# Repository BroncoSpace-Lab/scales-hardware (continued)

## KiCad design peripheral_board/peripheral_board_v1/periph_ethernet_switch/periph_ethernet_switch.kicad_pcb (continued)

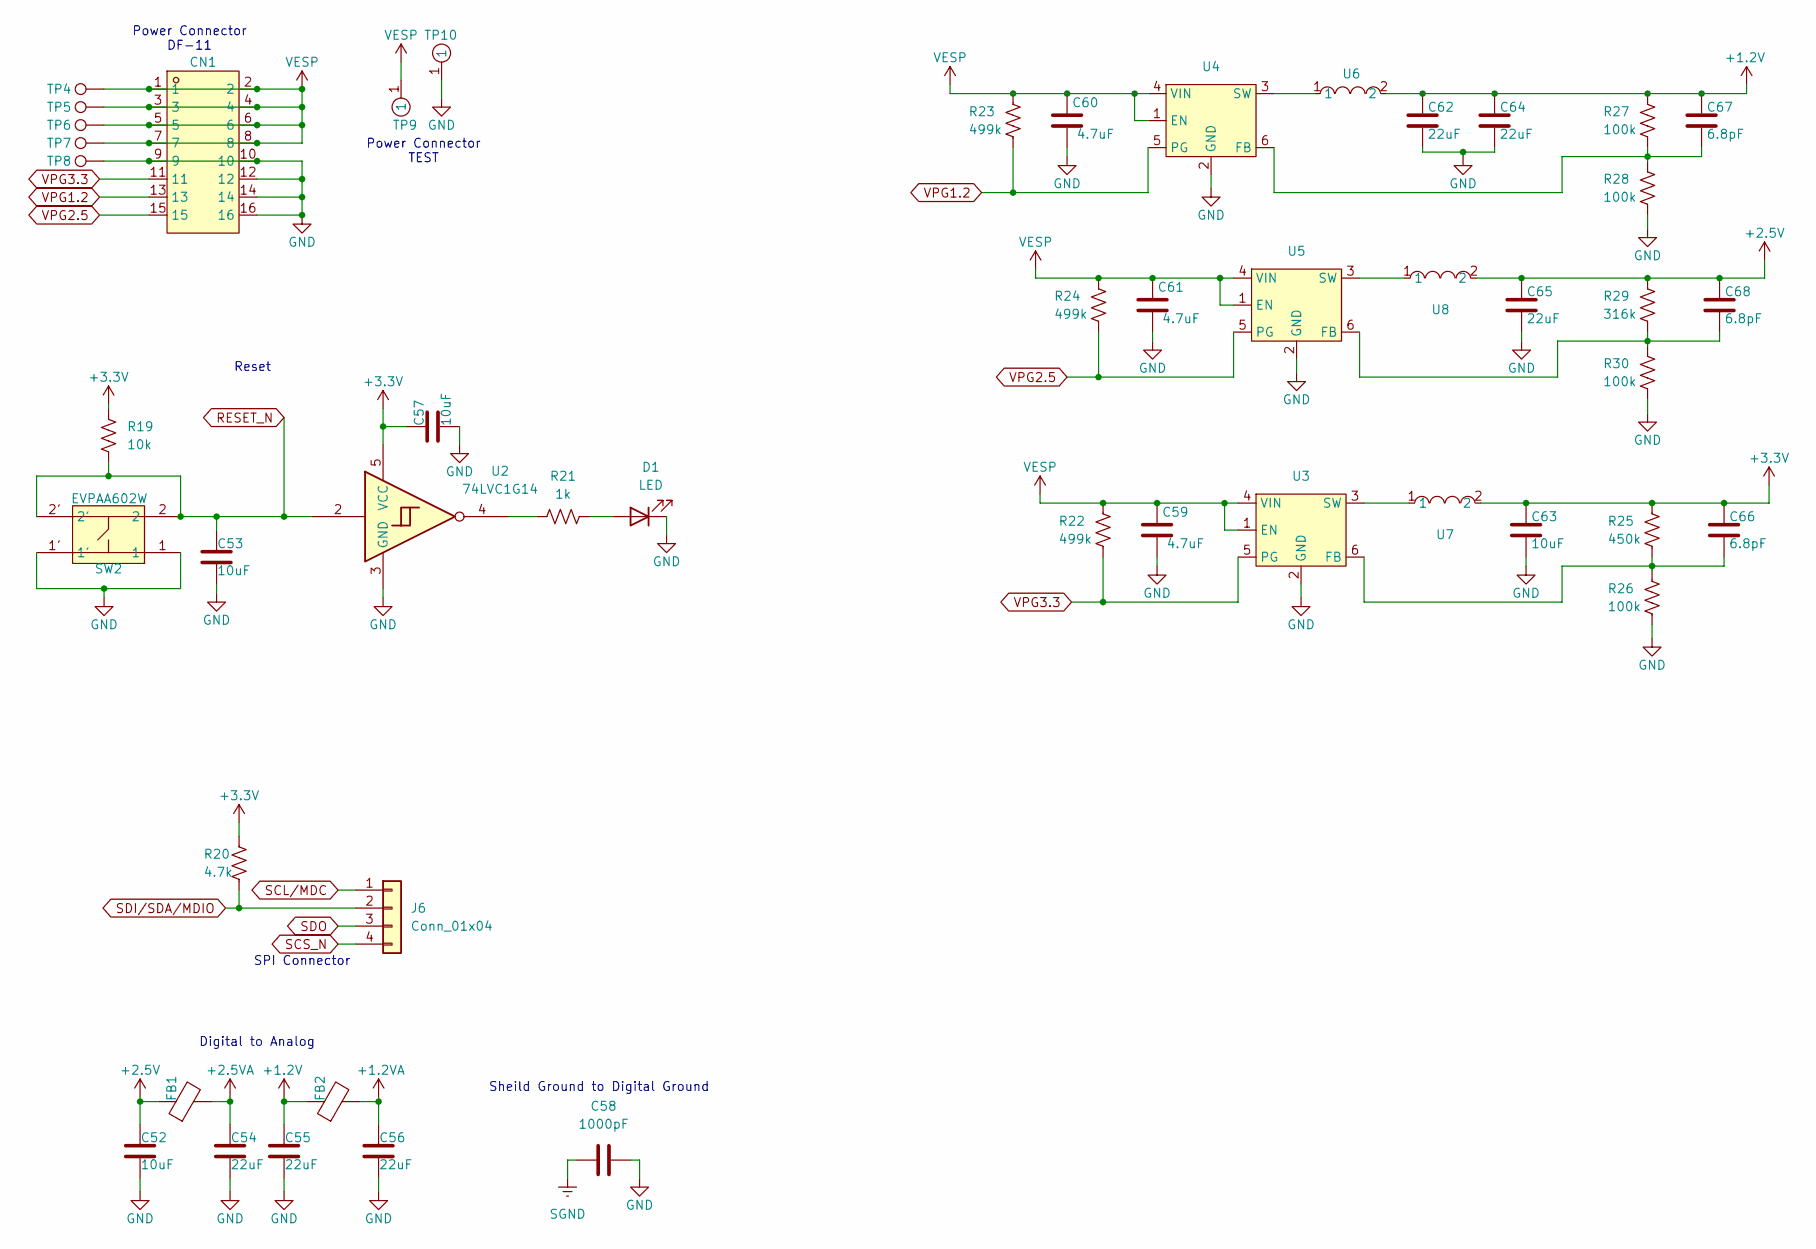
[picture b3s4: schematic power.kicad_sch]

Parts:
C52, C53, C57, C63: 10uF; C_0603_1608Metric
C54, C55, C56, C62, C64, C65: 22uF; C_0603_1608Metric
C58: 1000pF; C_1210_3225Metric
C59, C60, C61: 4.7uF; C_0603_1608Metric
C66, C67, C68: 6.8pF; C_0603_1608Metric
CN1: DF11-16DP-2DSA(08); CONN-TH_DF11-16DP-2DSA-08; LCSC Part C530981
D1: LED; LED0603-RD
FB1, FB2: FerriteBead; L_0805_2012Metric
J6: Conn_01x04; PinHeader_1x04_P2.54mm_Vertical
R19: 10k; R_0603_1608Metric
R20: 4.7k; R_0603_1608Metric
R21: 1k; R_0603_1608Metric
R22, R23, R24: 499k; R_0603_1608Metric
R25: 450k; R_0603_1608Metric
R26, R27, R28, R30: 100k; R_0603_1608Metric
R29: 316k; R_0603_1608Metric
SW2: EVPAA602W; KEY-TH_4P-L3.5-W4.9-P2.80-LS4.3; LCSC Part C79148
TP4, TP5, TP6, TP7, TP8: TestPoint; TestPoint_Pad_1.0x1.0mm
TP9, TP10: RH-5001; TEST-TH_BD2.54-P1.4_BLACK; LCSC Part C5199801
U2: 74LVC1G14; SOT-23-5
U3, U4, U5: TLV62569PDDCR; SOT-23-6_L2.9-W1.6-P0.95-LS2.8-BL; LCSC Part C398365
U6, U7, U8: XAL4020-222MEC; IND-SMD_L4.0-W4.0-A; LCSC Part C3151182

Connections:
+1.2V: C55.1, C62.1, C64.1, C67.1, FB2.1, R27.2, U6.2; also elsewhere on the board
+1.2VA: C56.1, FB2.2; also elsewhere on the board
+2.5V: C52.1, C65.1, C68.1, FB1.1, R29.2, U8.2
+2.5VA: C54.1, FB1.2; also elsewhere on the board
unnamed: D1.2 (A), R21.1
unnamed: R21.2, U2.4
unnamed: U3.3 (SW), U7.1
unnamed: C67.2, R27.1, R28.2, U4.6 (FB)
unnamed: U4.3 (SW), U6.1
unnamed: C68.2, R29.1, R30.2, U5.6 (FB)
unnamed: U5.3 (SW), U8.1
RESET_N: C53.1, R19.1, SW2.2, SW2.2', U2.2; also elsewhere on the board
SCL/MDC: J6.1; also elsewhere on the board
SCS_N: J6.4; also elsewhere on the board
SDI/SDA/MDIO: J6.2, R20.1; also elsewhere on the board
SDO: J6.3; also elsewhere on the board
SGND: C58.1; also elsewhere on the board
VESP: C59.1, C60.1, C61.1, CN1.1, CN1.2, CN1.3, CN1.4, CN1.5, CN1.6, CN1.7, CN1.8, R22.2, R23.2, R24.2, TP4.1, TP5.1, TP6.1, TP7.1, TP9.1, U3.1 (EN), U3.4 (VIN), U4.1 (EN), U4.4 (VIN), U5.1 (EN), U5.4 (VIN)
VPG1.2: CN1.13, R23.1, U4.5 (PG)
VPG2.5: CN1.15, R24.1, U5.5 (PG)
VPG3.3: CN1.11, R22.1, U3.5 (PG)

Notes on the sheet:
Reset
SPI Connector
Sheild Ground to Digital Ground
Digital to Analog
Power Connector DF-11
Power Connector TEST

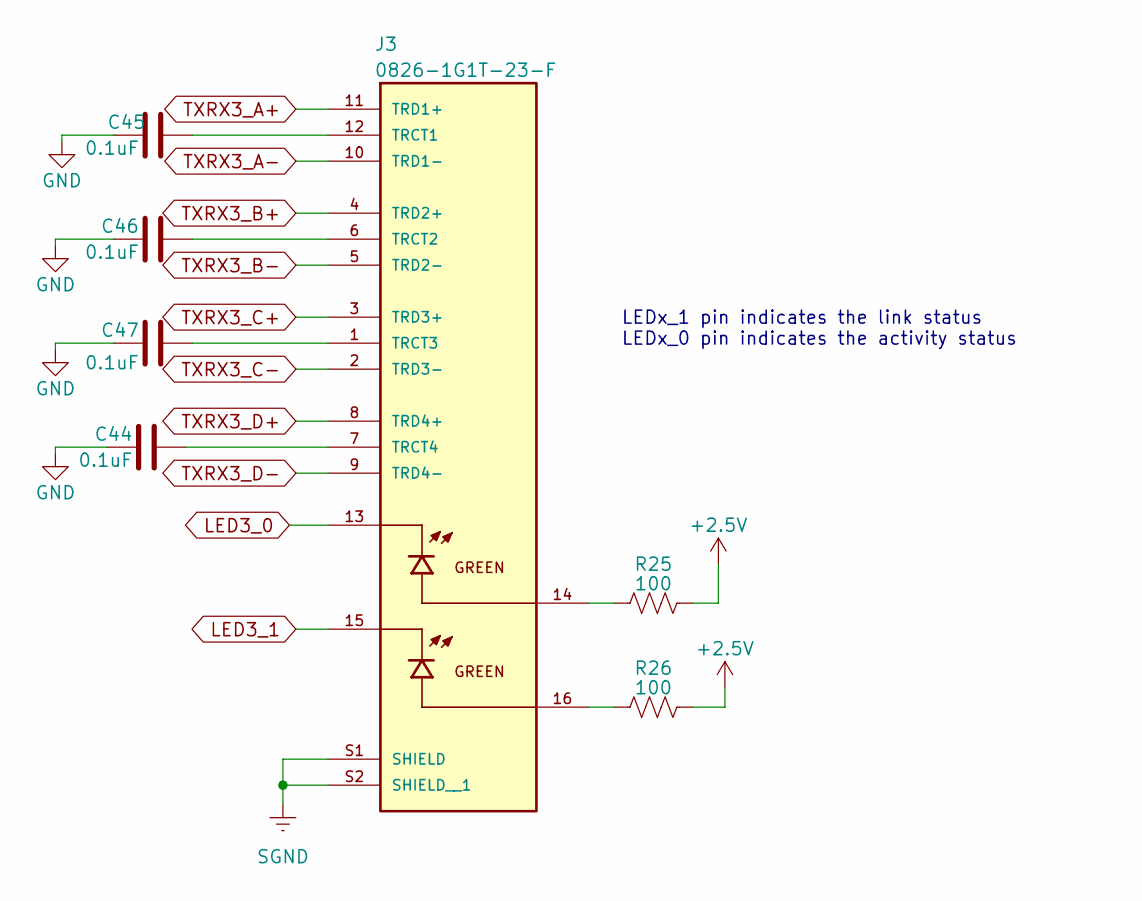
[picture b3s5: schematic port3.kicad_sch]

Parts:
C44, C45, C46, C47: 0.1uF; C_0603_1608Metric
J3: 0826-1G1T-23-F; BEL_0826-1G1T-23-F
R25, R26: 100; R_0603_1608Metric

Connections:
LED3_0: J3.13; also elsewhere on the board
LED3_1: J3.15; also elsewhere on the board
SGND: J3.S1 (SHIELD), J3.S2 (SHIELD__1); also elsewhere on the board
TXRX3_A+: J3.11 (TRD1+); also elsewhere on the board
TXRX3_A-: J3.10 (TRD1-); also elsewhere on the board
TXRX3_B+: J3.4 (TRD2+); also elsewhere on the board
TXRX3_B-: J3.5 (TRD2-); also elsewhere on the board
TXRX3_C+: J3.3 (TRD3+); also elsewhere on the board
TXRX3_C-: J3.2 (TRD3-); also elsewhere on the board
TXRX3_D+: J3.8 (TRD4+); also elsewhere on the board
TXRX3_D-: J3.9 (TRD4-); also elsewhere on the board

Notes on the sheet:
LEDx_1 pin indicates the link status LEDx_0 pin indicates the activity status

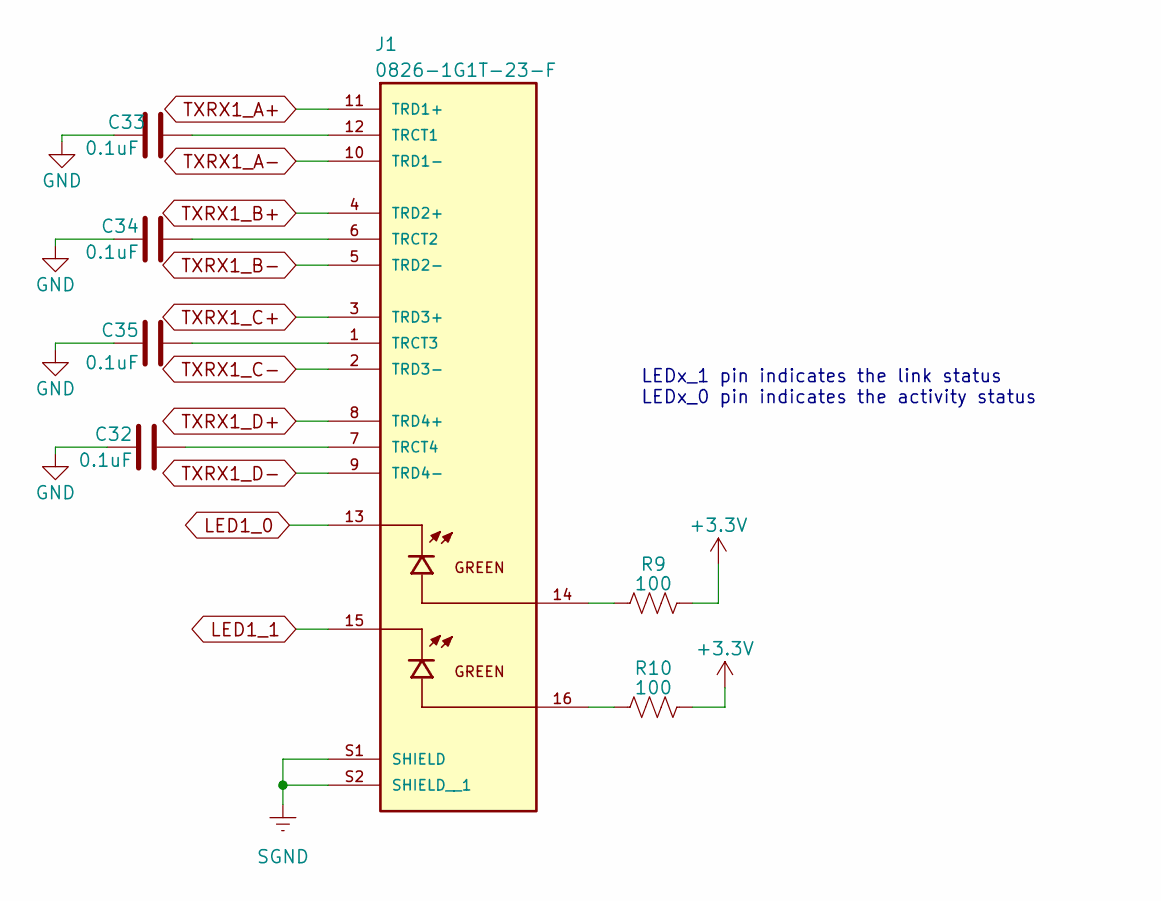
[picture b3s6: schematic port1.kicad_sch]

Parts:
C32, C33, C34, C35: 0.1uF; C_0603_1608Metric
J1: 0826-1G1T-23-F; BEL_0826-1G1T-23-F
R9, R10: 100; R_0603_1608Metric

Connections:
LED1_0: J1.13; also elsewhere on the board
LED1_1: J1.15; also elsewhere on the board
unnamed: J1.14, R9.2
unnamed: J1.16, R10.2
unnamed: C33.2, J1.12 (TRCT1)
unnamed: C34.2, J1.6 (TRCT2)
unnamed: C35.2, J1.1 (TRCT3)
unnamed: C32.2, J1.7 (TRCT4)
SGND: J1.S1 (SHIELD), J1.S2 (SHIELD__1); also elsewhere on the board
TXRX1_A+: J1.11 (TRD1+); also elsewhere on the board
TXRX1_A-: J1.10 (TRD1-); also elsewhere on the board
TXRX1_B+: J1.4 (TRD2+); also elsewhere on the board
TXRX1_B-: J1.5 (TRD2-); also elsewhere on the board
TXRX1_C+: J1.3 (TRD3+); also elsewhere on the board
TXRX1_C-: J1.2 (TRD3-); also elsewhere on the board
TXRX1_D+: J1.8 (TRD4+); also elsewhere on the board
TXRX1_D-: J1.9 (TRD4-); also elsewhere on the board

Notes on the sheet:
LEDx_1 pin indicates the link status LEDx_0 pin indicates the activity status

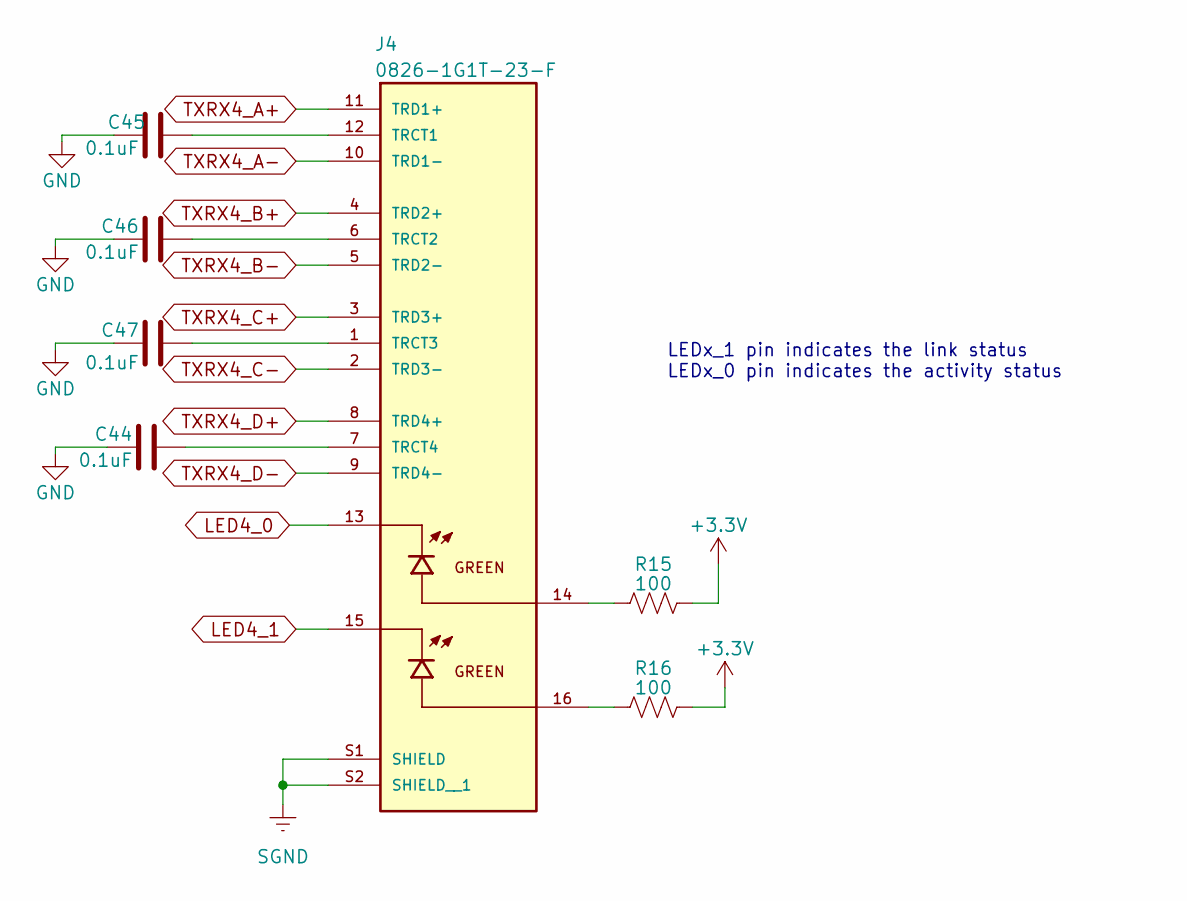
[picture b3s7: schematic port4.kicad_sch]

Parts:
C44, C45, C46, C47: 0.1uF; C_0603_1608Metric
J4: 0826-1G1T-23-F; BEL_0826-1G1T-23-F
R15, R16: 100; R_0603_1608Metric

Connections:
LED4_0: J4.13; also elsewhere on the board
LED4_1: J4.15; also elsewhere on the board
unnamed: J4.14, R15.2
unnamed: J4.16, R16.2
SGND: J4.S1 (SHIELD), J4.S2 (SHIELD__1); also elsewhere on the board
TXRX4_A+: J4.11 (TRD1+); also elsewhere on the board
TXRX4_A-: J4.10 (TRD1-); also elsewhere on the board
TXRX4_B+: J4.4 (TRD2+); also elsewhere on the board
TXRX4_B-: J4.5 (TRD2-); also elsewhere on the board
TXRX4_C+: J4.3 (TRD3+); also elsewhere on the board
TXRX4_C-: J4.2 (TRD3-); also elsewhere on the board
TXRX4_D+: J4.8 (TRD4+); also elsewhere on the board
TXRX4_D-: J4.9 (TRD4-); also elsewhere on the board

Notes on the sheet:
LEDx_1 pin indicates the link status LEDx_0 pin indicates the activity status

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
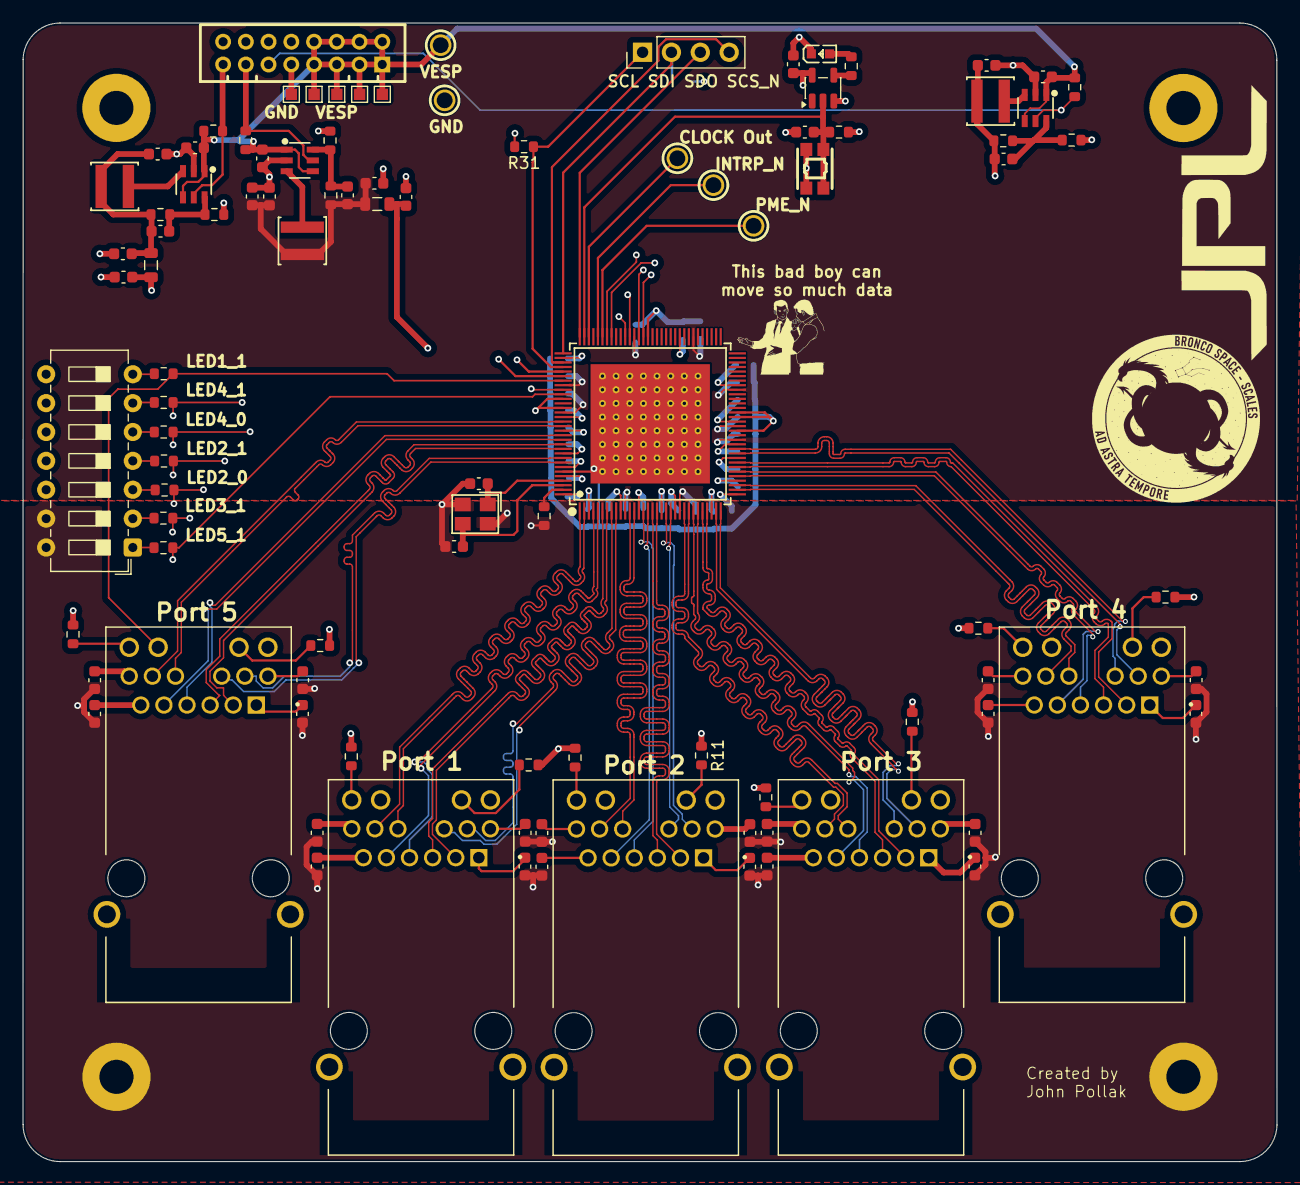
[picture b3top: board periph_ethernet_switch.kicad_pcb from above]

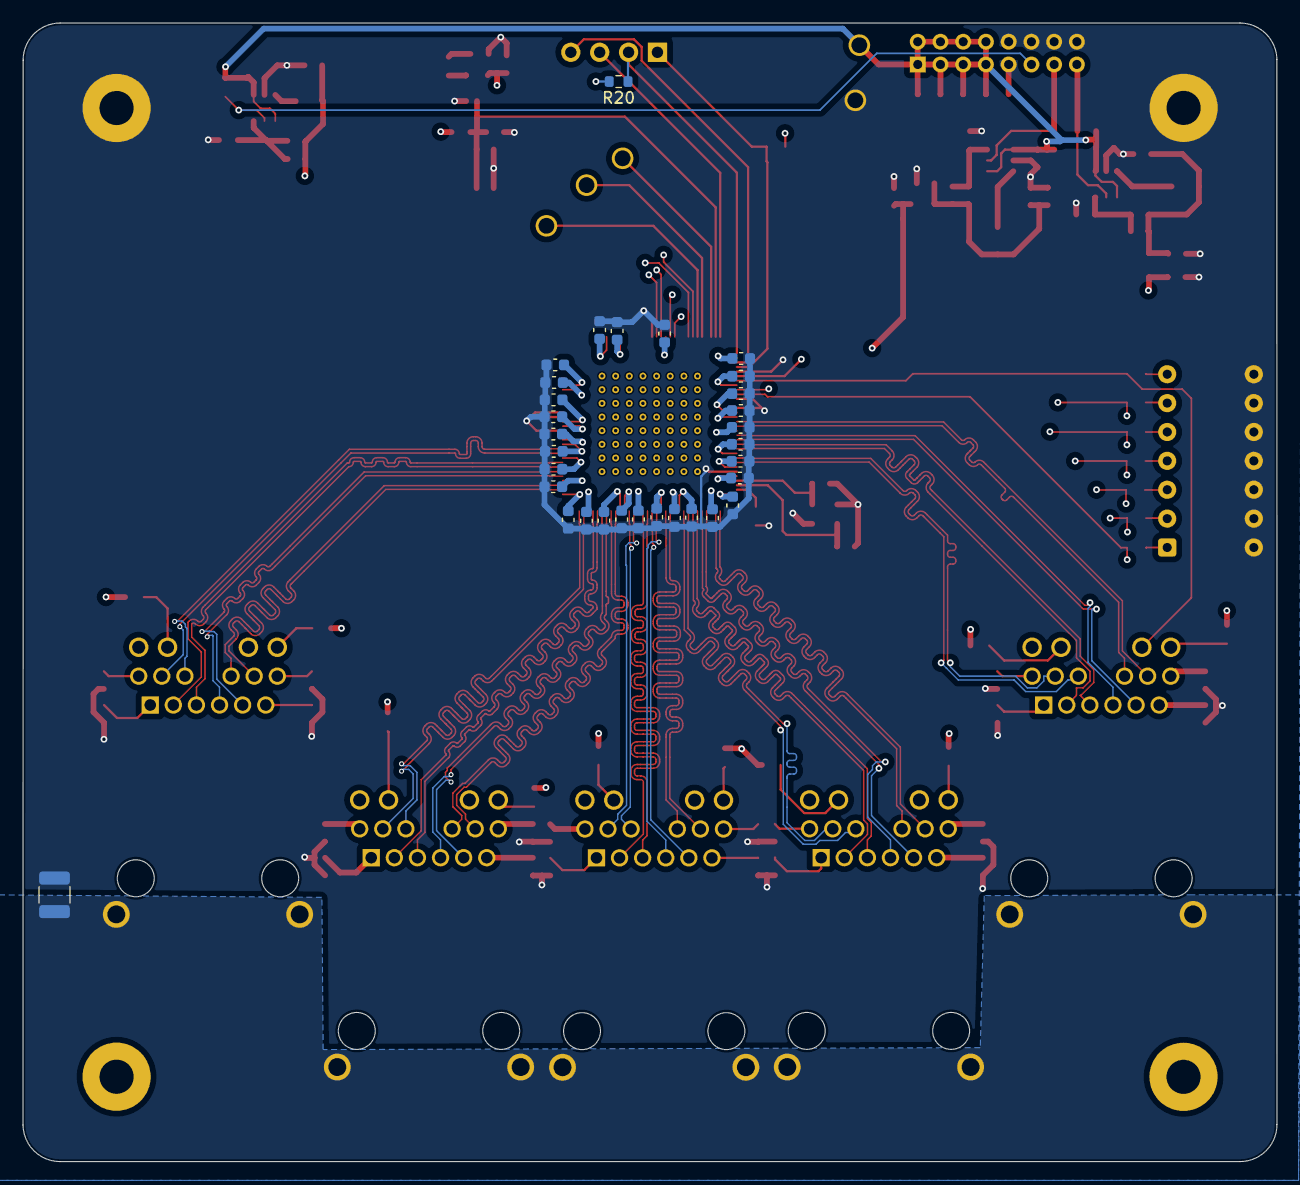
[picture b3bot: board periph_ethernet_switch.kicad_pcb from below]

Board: 6 copper layers, 110.3 x 100.2 mm, 134 parts (31 on the bottom side), 117 nets.

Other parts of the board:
C40, C41, C42, C43: 0.1uF; C_0603_1608Metric
R13, R14: 100; R_0603_1608Metric
R31: 4.7k; R_0603_1608Metric

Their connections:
SCL/MDC: R31.1; also elsewhere on the board

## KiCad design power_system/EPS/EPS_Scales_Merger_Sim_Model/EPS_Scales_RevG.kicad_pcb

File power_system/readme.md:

- **Viking 1-C Board Ordered (7/9/25)**
    
    This is the third board of the SCALES EPS. It is based on the RevF schematic which yields the Viking 1-C Board. This board improves on the success of the 1-B board and implements some minor improvements that prevented the Peripheral and Jetson subsystem from activating correctly. 
    
    **List of Changes in Viking 1-C After Production Errors in Viking 1-B**
    
    - Removed R48
    - Removed R83
    - The above mentioned resistors caused too low of a voltage to fully enable the En pins on the load switches, and by simply removing them we can successfully drive the load switches on using GPIO pins.
    - Added 3 MCP9808 I2C Temperature Sensors so we can have some on board temp monitoring, I made sure the addresses dont conflict with that of the other i2c devices on board.
    
    **EPS REV F/ Viking 1-C System Overview:**
    
    - Power Requirements (+28v 8A Max)
        - ML/Edge Computer - Nvidia Jetson (+20V 4A)
        - OBC/Flight Computer - IMX8 (+3.3V 2A)
        - Peripheral System - Raspberry Pi + Wiznet (+5V 2A)
    - Component List
        - Load Switch + Controller: [TPS1HA08-Q1](https://www.ti.com/lit/ds/symlink/tps1ha08-q1.pdf?ts=1748448912035&ref_url=https%253A%252F%252Fwww.ti.com%252Fproduct%252FTPS1HA08-Q1)
        - Switching Regulator: [LT8612](https://jlcpcb.com/api/file/downloadByFileSystemAccessId/8589836477510287360)
        - IV-Sensor: [INA260AIPWR](https://jlcpcb.com/api/file/downloadByFileSystemAccessId/8589836477510287360)
        - Temperature Sensor: [MCP9808](https://www.microchip.com/en-us/product/mcp9800)
        - Clock Generator: [LTC6902](https://www.analog.com/media/en/technical-documentation/data-sheets/6902f.pdf)
        - I2C Buffer: [TCA4307](https://www.ti.com/lit/ds/symlink/tca4307.pdf?HQS=dis-dk-null-digikeymode-dsf-pf-null-wwe&ts=1748986173530&ref_url=https%253A%252F%252Fwww.ti.com%252Fgeneral%252Fdocs%252Fsuppproductinfo.tsp%253FdistId%253D10%2526gotoUrl%253Dhttps%253A%252F%252Fwww.ti.com%252Flit%252Fgpn%252Ftca4307)
        - Comparator (WD Circuit): [TLV1704](https://www.ti.com/lit/ds/symlink/tlv1704-sep.pdf)
        - Subsystem Connector: [DF-11 (2x8)](https://www.lcsc.com/product-detail/Wire-To-Board-Wire-To-Wire-Connector_HRS-Hirose-HRS-DF11-16DP-2DSA-08_C530981.html)
        - Power Connector: [XT-60PWF](https://www.lcsc.com/product-detail/plug_Changzhou-Amass-Elec-XT60PW-F_C428722.html)
    - Concept of Operations
        - OBC is the primary subsystem, which is always enabled. The OBC controls the ML and Perif. via load switches. OBC must hold the respective subsystem EN pin high for it to be active.
        - Each subsystem has a Watch dog that verifies its normal operation; in the case of a fault, the subsystem is disabled by its watch dog.
            - OBC: If the OBC hangs and fails to pet, it is power cycled, as the EN pin for its load switch is always held high with respect to the battery voltage
            - ML/Perif: If either of these subsystems hang and fail to pet, they are disabled until the OBC re-enables them.
        - Monitoring is done by the OBC via I2C from the INA260s, which allows the subsystem to get basic telemetry on the subsystem state of operation
        - There are also 3 seperate temperature sensors that send telemetry back to the IMX8X over a 3.3v I2C
    
    **Block Diagram and Visual Con. Ops**
    
    - EPS RevF Block Diagram

    - EPS RevF Concept of Operations

    **Board Schematic**
    
    - Root

    - OBC Subsystem

    - Perif. Subsystem

    - Jetson Subsystem

    - OBC Watchdog Circuit

    - Peripheral Watchdog Circuit

    - Jetson Watchdog Circuit

    **Board Layout**
    
    - Signal1 Layer

    - GND Layer

    - Power Layer

    - Signal2 Layer

    **3D Render Front and Back**
    
    - Front

    - Back

###  Viking 1-B Board Ordered (6/20/25) ###
This is the second board of the SCALES EPS. It is based on the RevE schematic which yields the Viking 1-B Board. It seeks to improve on numerous calculation and placement errors in the first prototype. Particularly miscalculated resistor and inductor values as well as significant improvements in placement, routing, fills, and smaller components.

### List of Changes in Viking 1-B After Production Errors in Viking 1-A ###
* R66 was incorrect in 1-A, should have been a 100k, was a 10k instead. Fixed in this revision
* L2 was 8.2uH, should have been 6.1uH (OBC Subsystem)
* L1 was 12uH, should have been 10uH (Perif. Subsystem)
* L3 was 4.7uH, should have been 47uH (Jetson Subsystem)
* Most capacitors were changed to 50V/35V rated 0603 caps, any others are 10v 0402 caps.
* Small change to the Jetson WD circuit, adding a voltage divider to make the voltage safe for the the 10v 0402 caps
* Soft start capacitor was changed for each subsystem, set to 2.2uF for about 1 second. Using the V(t) = (I/C) * t equation, rearrange for t, and I is 2.1*10^-6, C is 2.2uF, and V(t) is 0.97v.
* LEDs on ST pin for all load switches were rearranged for (hopefully) proper fault indication
* 4.7k resistor removed for the I2C buffer
* Connectors were changed for identical variants of the 2*8 Df11 due to low stock
* D1N141WS diodes were changes to D1N4448WS diodes. Almost identical, same package
* Replaced mounting holes with slightly larger ones to match the M2.5 Spec (2.7mm hole diameter)

## EPS_REVE / Viking 1-BSystem Overview: ##

- Power Requirements (+28v 8A Max)
    - ML/Edge Computer - Nvidia Jetson (+20V 4A)
    - OBC/Flight Computer - IMX8 (+3.3V 2A)
    - Peripheral System - Raspberry Pi + Wiznet (+5V 2A)
- Component List
    - Load Switch + Controller: [TPS1HA08-Q1](https://www.ti.com/lit/ds/symlink/tps1ha08-q1.pdf?ts=1748448912035&ref_url=https%253A%252F%252Fwww.ti.com%252Fproduct%252FTPS1HA08-Q1)
    - Switching Regulator: [LT8612](https://jlcpcb.com/api/file/downloadByFileSystemAccessId/8589836477510287360)
    - IV-Sensor: [INA260AIPWR](https://jlcpcb.com/api/file/downloadByFileSystemAccessId/8589836477510287360)
    - Clock Generator: [LTC6902](https://www.analog.com/media/en/technical-documentation/data-sheets/6902f.pdf)
    - I2C Buffer: [TCA4307](https://www.ti.com/lit/ds/symlink/tca4307.pdf?HQS=dis-dk-null-digikeymode-dsf-pf-null-wwe&ts=1748986173530&ref_url=https%253A%252F%252Fwww.ti.com%252Fgeneral%252Fdocs%252Fsuppproductinfo.tsp%253FdistId%253D10%2526gotoUrl%253Dhttps%253A%252F%252Fwww.ti.com%252Flit%252Fgpn%252Ftca4307)
    - Comparator (WD Circuit): [TLV1704](https://www.ti.com/lit/ds/symlink/tlv1704-sep.pdf)
    - Subsystem Connector: [DF-11 (2x8)](https://www.lcsc.com/product-detail/Wire-To-Board-Wire-To-Wire-Connector_HRS-Hirose-HRS-DF11-16DP-2DSA-08_C530981.html)
    - Power Connector: [XT-60PWF](https://www.lcsc.com/product-detail/plug_Changzhou-Amass-Elec-XT60PW-F_C428722.html)
- Concept of Operations
    - OBC is the primary subsystem, which is always enabled. The OBC controls the ML and Perif. via load switches. OBC must hold the respective subsystem EN pin high for it to be active.
    - Each subsystem has a Watch dog that verifies its normal operation; in the case of a fault, the subsystem is disabled by its watch dog.
        - OBC: If the OBC hangs and fails to pet, it is power cycled, as the EN pin for its load switch is always held high with respect to the battery voltage
        - ML/Perif: If either of these subsystems hang and fail to pet, they are disabled until the OBC re-enables them.
    - Monitoring is done by the OBC via I2C from the INA260s, which allows the subsystem to get basic telemetry on the subsystem state of operation

## Block Diagram and Visual Con. Ops ##

* EPS RevE Block Diagram

* EPS RevD Concept of Operations

## **Board Schematic** ##
* Root

* OBC Subsystem

* Perif. Subsystem

* Jetson Subsystem

* OBC Watchdog Circuit

* Peripheral Watchdog Circuit

* Jetson Watchdog Circuit

## **Board Layout** ##

* Signal1 Layer

* GND Layer

    )
    
* Power Layer

* Signal2 Layer

## 3D Render Front and Back ##
    
* Front

* Back   

## **Testing and Evaluation**

Using the on board test points in the schematic, we can check if all the voltages behave as designed. Use the below references to check if the expectations are met.

Overall Board:

- [ ]  TP 31, 39, 25  → 28v (Vbatt)
- [ ]  Mounting Holes → GND

OBC Subsystem:

- [ ]  TP 36 → EN (Should be 28*10k/66.2k)
- [ ]  TP 32 → ~28v to Switching Regulator
- [ ]  TP 35 → SYNCPHASE1 (400Khz 0 deg out of phase)
- [ ]  TP 33 → Output of Switching regulator (~3.3V)
- [ ]  TP 34 → Output of INA260 (~3.3V)

WD_OBC:

- [ ]  TP 48 → Ensures WD is supplied with power
- [ ]  TP 49 → WD Input from OBC GPIO for pet
- [ ]  TP 53 → WD Open collector output, can only drive low, otherwise floating

Jetson Subsystem: 

- [ ]  TP 38 → Tests the GPIO input from the OBC/WD EN Pin (Should be held high when System is active, low on PET failure)
- [ ]  TP 25 → ~28v (Vbatt)
- [ ]  TP 26 → ~28v output from load switch
- [ ]  TP 27 → SYNCPHASE3 (400khz 180 deg out of phase from PHASE1)
- [ ]  TP28 → ~20v (Output from Switching regulator)
- [ ]  TP 29 → ~20v (Output from INA290 to Jetson Subsystem)
    
    WD_OBC:
    
    - [ ]  TP 10 → Check WD Supply power, should be 20v
    - [ ]  TP 11 → WD Interface input line, held high when there is a pet
    - [ ]  TP 47 Open collector output from the Watchdog, should be half of whatever the OBC GPIO pin voltage is when high, and then ground any other time

Peripheral Subsystem:

- [ ]  TP 39 → ~28v (Vbatt)
- [ ]  TP 82 → OBC GPIO input for EN line and WD En line, should be ~1.4v when high for OBC holding it high, and low when not held high.
- [ ]  TP 40 → ~28v output of the load switch
- [ ]  TP 41 → SYNCPHASE2 Output of LTC6902 (400khz 90 deg out of phase)
- [ ]  TP 42 → Input regulated power to the INA260, should be roughly +5v
- [ ]  TP 43 → output for the Peripheral subsystem, should be roughly +5v
    
    WD_Perif:
    
    - [ ]  TP 5 → 5v supply to power the watch dog
    - [ ]  TP 15 → WD Perif output always pulled low, should be low when the system is off, and held high when the OBC enables it, when the pet fails it will hold low until the subsystem turns off.

------------------------------------------------------------------------------------------------------------------------------------------

###  Viking 1-A Board Ordered (6/4/25) ###
The first board that was ordered was based on the EPS SCALES REV D schematic and is the Viking 1-A board.
This board can be found on github with the commit titled the same name.
This board does have some production issues which were already fixed and committed under the same name.
The production errors that this board include are simple, which is why they are included under the same board revision, they are simply lack of copper fills over the remaining area of the board which were corrected by the manufacturer. Post evaluation and testing of the Viking 1-A board will allow for next design implementation and lead to the Viking 1-B board.

### List of Changes After Production Errors for Viking 1-A ###
Copper fills were missing around the majority of non power traces and were causing difficulties in manufacuring, this was corrected by JLCPCB by their fab engineers, but I took the liberty of adding the same type of corrections to the existing board version. These are included in the latest commit.

## EPS_REVD / Viking 1-A System Overview: ##

- Power Requirements (+28v 8A Max)
    - ML/Edge Computer - Nvidia Jetson (+20V 4A)
    - OBC/Flight Computer - IMX8 (+3.3V 2A)
    - Peripheral System - Raspberry Pi + Wiznet (+5V 2A)
- Component List
    - Load Switch + Controller: [TPS1HA08-Q1](https://www.ti.com/lit/ds/symlink/tps1ha08-q1.pdf?ts=1748448912035&ref_url=https%253A%252F%252Fwww.ti.com%252Fproduct%252FTPS1HA08-Q1)
    - Switching Regulator: [LT8612](https://jlcpcb.com/api/file/downloadByFileSystemAccessId/8589836477510287360)
    - IV-Sensor: [INA260AIPWR](https://jlcpcb.com/api/file/downloadByFileSystemAccessId/8589836477510287360)
    - Clock Generator: [LTC6902](https://www.analog.com/media/en/technical-documentation/data-sheets/6902f.pdf)
    - I2C Buffer: [TCA4307](https://www.ti.com/lit/ds/symlink/tca4307.pdf?HQS=dis-dk-null-digikeymode-dsf-pf-null-wwe&ts=1748986173530&ref_url=https%253A%252F%252Fwww.ti.com%252Fgeneral%252Fdocs%252Fsuppproductinfo.tsp%253FdistId%253D10%2526gotoUrl%253Dhttps%253A%252F%252Fwww.ti.com%252Flit%252Fgpn%252Ftca4307)
    - Comparator (WD Circuit): [TLV1704](https://www.ti.com/lit/ds/symlink/tlv1704-sep.pdf)
    - Subsystem Connector: [DF-11 (2x8)](https://www.lcsc.com/product-detail/Wire-To-Board-Wire-To-Wire-Connector_HRS-Hirose-HRS-DF11-16DP-2DSA-08_C530981.html)
    - Power Connector: [XT-60PWF](https://www.lcsc.com/product-detail/plug_Changzhou-Amass-Elec-XT60PW-F_C428722.html)
- Concept of Operations
    - OBC is the primary subsystem, which is always enabled. The OBC controls the ML and Perif. via load switches. OBC must hold the respective subsystem EN pin high for it to be active.
    - Each subsystem has a Watch dog that verifies its normal operation; in the case of a fault, the subsystem is disabled by its watch dog.
        - OBC: If the OBC hangs and fails to pet, it is power cycled, as the EN pin for its load switch is always held high with respect to the battery voltage
        - ML/Perif: If either of these subsystems hang and fail to pet, they are disabled until the OBC re-enables them.
    - Monitoring is done by the OBC via I2C from the INA260s, which allows the subsystem to get basic telemetry on the subsystem state of operation

## Block Diagram and Visual Con. Ops ##

* EPS RevD Block Diagram

* EPS RevD Concept of Operations

## **Board Schematic** ##
* Root

* Jetson Subsystem

* OBC Subsystem

* Perif. Subsystem

* Watchdog Circuit

## **Board Layout** ##

* Signal1 Layer

* GND Layer

* Power Layer

* Signal2 Layer

## 3D Render Front and Back ##
    
* Front

* Back   

## **Testing and Evaluation**

Using the on board test points and the expected probe locations based on the schematic, we can check if all the voltages are as required, if the watch dogs are behaving as expected, and if there are any components that may not be performing as required.

Overall Board:

- [ ]  TP 25, 31, 39 → 28v (Vbatt)
- [ ]  Mounting Holes → GND

OBC Subsystem:

- [ ]  TP 36 → EN
- [ ]  TP 32 → ~28v to Switching Regulator
- [ ]  TP 35 → SYNCPHASE1 (400Khz 0 deg out of phase)
- [ ]  TP 33 → Output of Switching regulator (~3.3V)
- [ ]  TP 34 → Output of INA260 (~3.3V)

WD_OBC:

- [ ]  TP 48 → Ensures WD is supplied with power
- [ ]  TP 49 → WD Input from OBC GPIO for pet
- [ ]  TP 53 → WD Open collector output, can only drive low, otherwise floating

Jetson Subsystem: 

- [ ]  TP 38 → Tests the GPIO input from the OBC/WD EN Pin (Should be held high when System is active, low on PET failure)
- [ ]  TP 25 → ~28v (Vbatt)
- [ ]  TP 26 → ~28v output from load switch
- [ ]  TP 27 → SYNCPHASE3 (400khz 180 deg out of phase from PHASE1)
- [ ]  TP28 → ~20v (Output from Switching regulator)
- [ ]  TP 29 → ~20v (Output from INA290 to Jetson Subsystem)
    
    WD_OBC:
    
    - [ ]  TP 10 → Check WD Supply power, should be 20v
    - [ ]  TP 11 → WD Interface input line, held high when there is a pet
    - [ ]  TP 47 Open collector output from the Watchdog, should be half of whatever the OBC GPIO pin voltage is when high, and then ground any other time

Peripheral Subsystem:

- [ ]  TP 39 → ~28v (Vbatt)
- [ ]  TP 82 → OBC GPIO input for EN line and WD En line, should be ~1.4v when high for OBC holding it high, and low when not held high.
- [ ]  TP 40 → ~28v output of the load switch
- [ ]  TP 41 → SYNCPHASE2 Output of LTC6902 (400khz 90 deg out of phase)
- [ ]  TP 42 → Input regulated power to the INA260, should be roughly +5v
- [ ]  TP 43 → output for the Peripheral subsystem, should be roughly +5v
    
    WD_Perif:
    
    - [ ]  TP 5 → 5v supply to power the watch dog
    - [ ]  TP 15 → WD Perif output always pulled low, should be low when the system is off, and held high when the OBC enables it, when the pet fails it will hold low until the subsystem turns off.

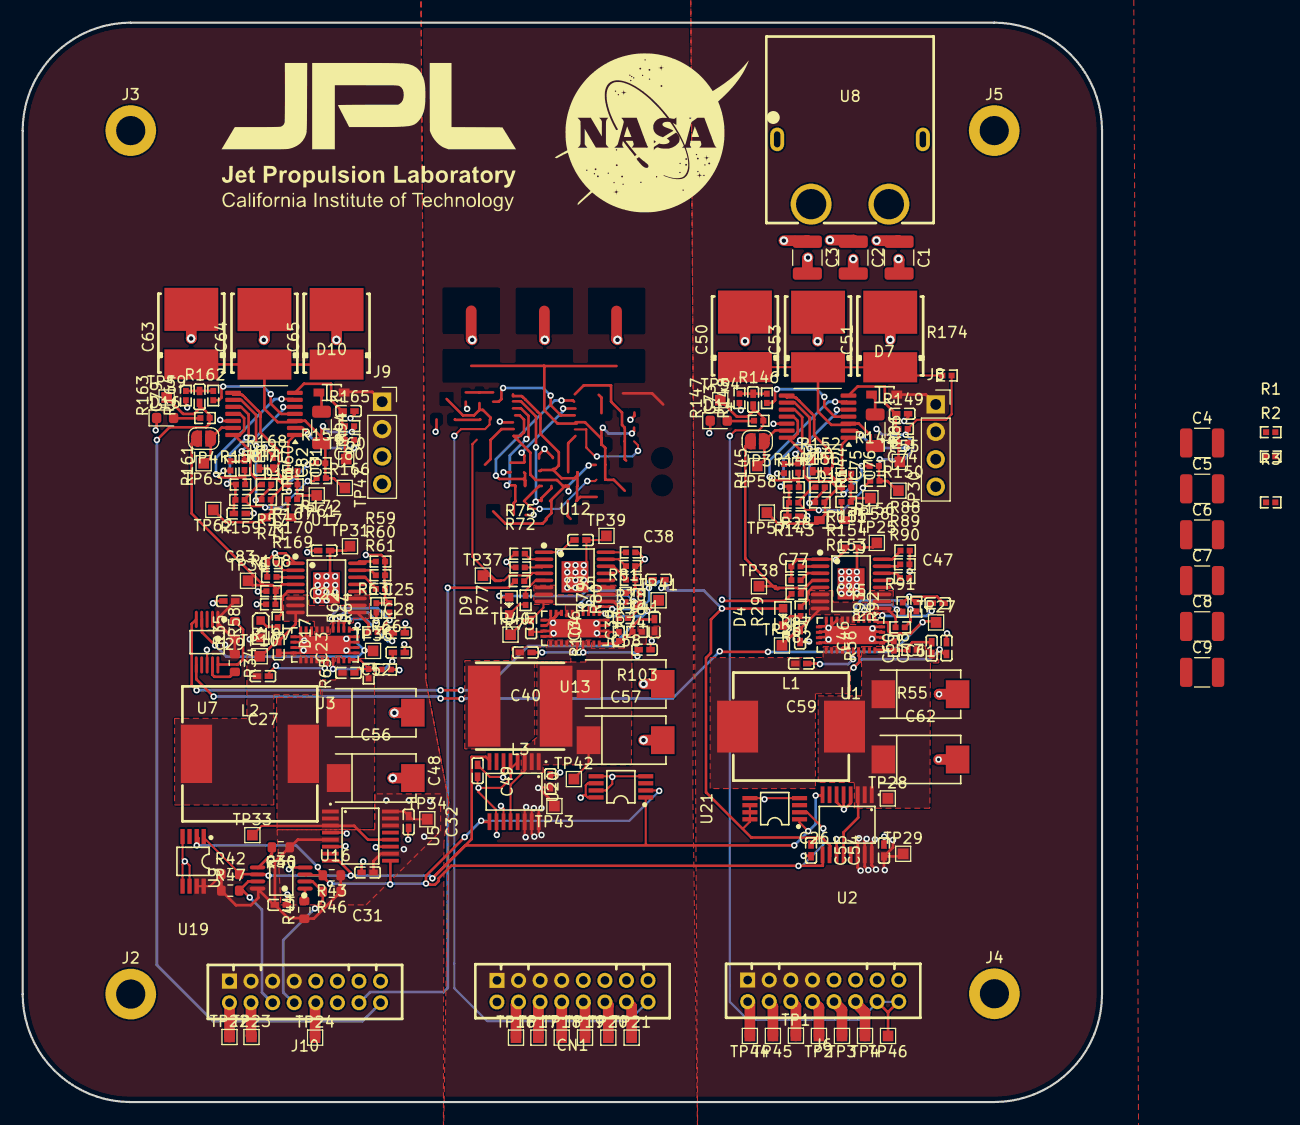
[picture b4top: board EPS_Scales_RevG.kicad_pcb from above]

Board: 4 copper layers, 100.0 x 100.0 mm, 226 parts (0 on the bottom side), 123 nets.

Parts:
C1, C2, C3, C4, C5, C6, C7, C8, C9: 10u; C_1210_3225Metric
C23, C36, C46: 22n; C0402
C24, C35, C45: 220n; C0402
C25, C38, C47: 2.2u; C0402
C26, C39, C60: 10p; C0402
C27, C28, C29, C30, C31, C32, C40, C41, C48, C49, C54, C55, C59, C78: 100n; C0402
C50, C51, C53, C63, C64, C65: 100uF; CAP-SMD_L7.3-W6.1_TCN4227M025R0100
C52, C56, C57, C58, C61, C62: 47u; CAP-SMD_L7.3-W4.3-FD
C73, C74, C75, C76, C77, C79, C80, C81, C82, C83: 10u; C0402
CN1: DF11-16DP-2DSA(08); CONN-TH_DF11-16DP-2DSA-08
D4, D9, D17: LED; LED0603-RD_RED
D7, D10, D15, D18: 1N4448WS-7-F; SOD-323_L1.8-W1.3-LS2.5-RD
D14, D16: GREEN; LED_0603_1608Metric
J2, J3, J4, J5: Conn_01x01_Socket; MountingHole_2.7mm_M2.5_DIN965_Pad
J6, J10: DF11-16DP-2DSA; CONN-TH_DF11-16DP-2DSA-08
J8, J9: Conn_01x04; PinSocket_1x04_P2.54mm_Vertical
JP3, JP4: SolderJumper_2_Open; SolderJumper-2_P1.3mm_Open_RoundedPad1.0x1.5mm
L1: 47uH; IND-SMD_L10.7-W10.0_ETQP5MXXXX
L2: 6.1u; IND-SMD_FTKB1207-6R1NT
L3: 10u; IND-SMD_L8.0-W8.0
R1, R3, R28, R29, R57, R58, R73, R75, R77, R82, R149, R151, R165, R167: 1k; R0402
R2, R41, R59, R60, R61, R72, R74, R76, R78, R87, R88, R89, R90: 15k; R0402
R34: 14k; R_0603_1608Metric
R35: 17k; R_0603_1608Metric
R42, R43, R44, R45, R46, R47: 4.7k; R_0603_1608Metric
R55: 196k; R0402
R56, R108, R141, R142, R143, R144, R147, R148, R157, R158, R159, R160, R163, R164: 10k; R0402
R62, R79, R93: 110k; R0402
R63, R81, R91: 47k; R0402
R64, R80, R92: 2k; R0402
R65: 240k; R0402
R66, R150, R152, R153, R155, R156, R166, R168, R169, R171, R172, R174: 100k; R0402
R86, R94: 10; R_1206_3216Metric
R103: 20.8k; R0402
R104: 5k; R0402
R107: 56.2k; R0402
R145, R146, R161, R162: 3k; R0402
R154, R170: 4.7M; R0402
TP1, TP2, TP3, TP4, TP10, TP16, TP17, TP18, TP19, TP20, TP21, TP22, TP23, TP24, TP25, TP26, TP27, TP28, TP29, TP30, TP31, TP33, TP34, TP35, TP36, TP37, TP38, TP39, TP40, TP41, TP42, TP43, TP44, TP45, TP46, TP47, TP54, TP55, TP56, TP57, TP58, TP59, TP60, TP61, TP62, TP63: TestPoint; TestPoint_Pad_1.0x1.0mm
U1, U3, U13: LT8612EUDE#PBF; QFN-28_L6.0-W3.0-P0.50-BL-EP
U2, U5, U16: INA260AIPWR; TSSOP-16_L5.0-W4.4-P0.65-LS6.4-BL-1
U7: LTC6902; MSOP-10_L3.0-W3.0-P0.50-LS5.0-BL
U8: XT60PW-F_C428722; TH_2P-XT60PW-F
U9: TCA4307DGKR; VSSOP-8_L3.0-W3.0-P0.65-LS4.9-BL
U10, U11: TLV1704; TSSOP-14_4.4x5mm_P0.65mm
U12, U15, U17: TPS1HB08BQPWPRQ1; HTSSOP-16_L5.0-W4.4-P0.65-LS6.4-TL-EP2.9
U19, U20, U21: MCP9808T-E/MS; MSOP-8_L3.0-W3.0-P0.65-LS4.9-BL

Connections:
+3.3V_OBC: C29.1, C30.1, C31.1, C32.1, C48.1, C54.1, D4.2 (A), D9.2 (A), D10.2 (A), D17.2 (A), J9.1, J9.2, J10.1, J10.3, J10.5, J10.7, R34.1, R35.1, R42.1, R43.1, R44.1, R45.1, R46.1, R47.1, TP34.1, U2.10 (VS), U5.5 (A0), U5.10 (VS), U5.14 (IN-), U7.1 (V+), U9.8 (VCC), U16.4 (A1), U16.5 (A0), U16.10 (VS), U19.7 (A0), U19.8 (VDD), U20.6 (A1), U20.8 (VDD), U21.6 (A1), U21.7 (A0), U21.8 (VDD)
+5V_Perif: C49.1, CN1.1, CN1.3, CN1.5, CN1.7, TP43.1, U16.14 (IN-)
+20V_Jetson: C55.1, D7.2 (A), J6.1, J6.3, J6.5, J6.7, J8.1, J8.2, TP29.1, U2.14 (IN-)
+V_Batt: C1.1, C2.1, C3.1, C4.1, C5.1, C6.1, C7.1, C8.1, C9.1, C24.1, C35.1, C45.1, R107.2, TP25.1, TP31.1, TP39.1, U8.3 (+), U12.17 (VBB), U15.17 (VBB), U17.17 (VBB)
/Jetson_Subsystem/WD_Jetson/WDT-VIN: R141.2, R150.1, R156.1, R174.2, TP30.1
/Jetson_Subsystem/WD_Jetson/WDT-VP: R144.1, R145.2, U10.5 (+)
/OBC_Subsystem/WD_OBC/WDT-VIN: C63.1, C64.1, C65.1, R94.2, R157.2, R166.1, R172.1, TP47.1, U11.3 (V+)
/OBC_Subsystem/WD_OBC/WDT-VP: R160.1, R161.2, U11.5 (+)
GND: C1.2, C2.2, C3.2, C4.2, C5.2, C6.2, C7.2, C8.2, C9.2, C23.2, C24.2, C25.2, C28.2, C29.2, C30.2, C31.2, C32.2, C35.2, C36.2, C38.2, C41.2, C45.2, C46.2, C47.2, C48.2, C49.2, C50.2, C51.2, C52.2, C53.2, C54.2, C55.2, C56.2, C57.2, C58.2, C61.2, C62.2, C63.2, C64.2, C65.2, C74.1, C75.1, C76.1, C77.1, C78.2, C80.1, C81.1, C82.1, C83.1, CN1.9, CN1.11, CN1.13, CN1.15, D14.1 (K), D16.1 (K), J2.1, J3.1, J4.1, J5.1, J6.9, J6.11, J6.13, J6.15, J8.3, J8.4, J9.3, J9.4, J10.9, J10.11, J10.13, J10.15, R2.2, R28.1, R41.1, R56.2, R57.1, R59.2, R60.2, R61.2, R62.2, R64.2, R66.2, R72.1, R74.1, R75.1, R76.1, R78.1, R79.2, R80.2, R87.2, R88.2, R89.2, R90.2, R92.2, R93.2, R104.2, R108.1, R145.1, R147.1, R161.1, R163.1, U1.8 (PGND), U1.11 (GND), U1.25 (NC), U2.4 (A1), U2.5 (A0), U2.6 (GND), U3.8 (PGND), U3.11 (GND), U3.25 (NC), U5.4 (A1), U5.6 (GND), U7.8 (GND), U8.1, U8.2, U8.4 (-), U9.4 (GND), U10.12 (V-), U11.12 (V-), U12.1 (GND), U13.8 (PGND), U13.11 (GND), U13.25 (NC), U15.1 (GND), U16.6 (GND), U17.1 (GND), U19.4 (GND), U19.5 (A2), U19.6 (A1), U20.4 (GND), U20.5 (A2), U20.7 (A0), U21.4 (GND), U21.5 (A2)
unnamed: C73.2, R147.2, R148.2
unnamed: C79.2, R163.2, R164.2
unnamed: CN1.4, TP16.1
unnamed: CN1.6, TP17.1
unnamed: CN1.8, TP18.1
unnamed: CN1.10, TP19.1
unnamed: CN1.12, TP20.1
unnamed: CN1.14, TP21.1
unnamed: D4.1 (K), R29.1
unnamed: D7.1 (C), R86.1
unnamed: D9.1 (K), R77.1
unnamed: D10.1 (C), R94.1
unnamed: D14.2 (A), R146.1
unnamed: D15.2 (A), R153.2
unnamed: D15.1 (C), R154.2, R155.2, R156.2, TP57.1, U10.11 (+), U10.14
unnamed: D16.2 (A), R162.1
unnamed: D17.1 (K), R58.1
unnamed: D18.2 (A), R169.2
unnamed: D18.1 (C), R170.2, R171.2, R172.2, TP62.1, U11.11 (+), U11.14
unnamed: J6.2, TP44.1
unnamed: J6.4, TP45.1
unnamed: J6.6, TP1.1
unnamed: J6.8, TP2.1
unnamed: J6.10, TP3.1
unnamed: J6.12, TP4.1
unnamed: J10.2, TP22.1
unnamed: J10.4, TP23.1
unnamed: J10.10, TP24.1
unnamed: JP3.1 (A), TP58.1, U10.13
unnamed: JP4.1 (A), TP63.1, U11.13
unnamed: R141.1, R142.2, R152.1
unnamed: R149.2, U10.2
unnamed: R151.2, U10.1
unnamed: R157.1, R158.2, R168.1
unnamed: R165.2, U11.2
unnamed: R167.2, U11.1
unnamed: C60.1, C61.1, C62.1, L1.2, R55.1, TP28.1, U1.22 (BIAS), U2.1 (IN+), U2.12 (VBUS)
unnamed: C59.1, U1.20 (BST)
unnamed: R91.2, R92.1, U1.4 (EN/UV)
unnamed: C60.2, R55.2, R56.1, U1.24 (FB)
unnamed: C78.1, U1.21 (INTVCC)
unnamed: R93.1, U1.3 (RT)
unnamed: C59.2, L1.1, U1.15 (SW)
unnamed: C47.1, U1.2 (TR/SS)
unnamed: C46.1, R91.1, TP26.1, U1.5 (VIN), U15.6 (VOUT)
unnamed: C26.1, C52.1, C56.1, L2.2, R65.1, TP33.1, U3.22 (BIAS), U5.1 (IN+), U5.12 (VBUS)
unnamed: C27.1, U3.20 (BST)
unnamed: R63.2, R64.1, U3.4 (EN/UV)
unnamed: C26.2, R65.2, R66.1, U3.24 (FB)
unnamed: C28.1, U3.21 (INTVCC)
unnamed: R62.1, U3.3 (RT)
unnamed: C27.2, L2.1, U3.15 (SW)
unnamed: C25.1, U3.2 (TR/SS)
unnamed: R34.2, U7.9 (MOD)
unnamed: R35.2, U7.10 (SET)
unnamed: R44.2, U9.1 (EN)
unnamed: R45.2, U9.5 (READY)
unnamed: R148.1, U10.4 (-)
unnamed: C74.2, R149.1, R150.2, TP55.1, U10.7 (+)
unnamed: R143.1, R144.2, U10.6 (-)
unnamed: R152.2, R155.1, U10.9 (+)
unnamed: C75.2, C76.2, R151.1, R153.1, R154.1, TP56.1, U10.8 (-)
unnamed: C77.2, R142.1, R143.2, U10.10 (-)
unnamed: C50.1, C51.1, C53.1, R86.2, R174.1, U10.3 (V+)
unnamed: R164.1, U11.4 (-)
unnamed: C80.2, R165.1, R166.2, TP60.1, U11.7 (+)
unnamed: R159.1, R160.2, U11.6 (-)
unnamed: R168.2, R171.1, U11.9 (+)
unnamed: C81.2, C82.2, R167.1, R169.1, R170.1, TP61.1, U11.8 (-)
unnamed: C83.2, R158.1, R159.2, U11.10 (-)
unnamed: R78.2, U12.16 (DIA_EN)
unnamed: R73.1, TP37.1, U12.4 (EN)
unnamed: R72.2, U12.3 (LATCH)
unnamed: R74.2, U12.14 (SEL1)
unnamed: R76.2, U12.15 (SEL2)
unnamed: R75.2, U12.2 (SNS)
unnamed: C36.1, R81.1, TP40.1, U12.6 (VOUT), U13.5 (VIN)
unnamed: R77.2, U12.5 (~ST)
unnamed: C39.1, C57.1, C58.1, L3.2, R103.1, TP42.1, U13.22 (BIAS), U16.1 (IN+), U16.12 (VBUS)
unnamed: C40.1, U13.20 (BST)
unnamed: R80.1, R81.2, U13.4 (EN/UV)
unnamed: C39.2, R103.2, R104.1, U13.24 (FB)
unnamed: C41.1, U13.21 (INTVCC)
unnamed: R79.1, U13.3 (RT)
unnamed: C40.2, L3.1, U13.15 (SW)
unnamed: C38.1, U13.2 (TR/SS)
unnamed: R88.1, U15.16 (DIA_EN)
unnamed: R1.1, R2.1, R82.1, TP38.1, U15.4 (EN)
unnamed: R87.1, U15.3 (LATCH)
unnamed: R90.1, U15.14 (SEL1)
unnamed: R89.1, U15.15 (SEL2)
unnamed: R28.2, U15.2 (SNS)
unnamed: R29.2, U15.5 (~ST)
unnamed: R59.1, U17.16 (DIA_EN)
unnamed: R3.1, R107.1, R108.2, TP36.1, U17.4 (EN)
unnamed: R41.2, U17.3 (LATCH)
unnamed: R61.1, U17.14 (SEL1)
unnamed: R60.1, U17.15 (SEL2)
unnamed: R57.2, U17.2 (SNS)
unnamed: C23.1, R63.1, TP10.1, U3.5 (VIN), U17.6 (VOUT)
unnamed: R58.2, U17.5 (~ST)
OBC SCL: J10.8, R46.2, U9.2 (SCLOUT)
OBC SDA: J10.6, R47.2, U9.7 (SDAOUT)
OBC_EN_JETSON: J10.12, R82.2
OBC_EN_PERIF: J10.14, R73.2
SCL: R43.2, U2.9 (SCL), U5.9 (SCL), U9.3 (SCLIN), U16.9 (SCL), U19.2 (SCL), U20.2 (SCL), U21.2 (SCL)
SDA: R42.2, U2.8 (SDA), U5.8 (SDA), U9.6 (SDAIN), U16.8 (SDA), U19.1 (SDA), U20.1 (SDA), U21.1 (SDA)
SYNC_PHASE1: TP35.1, U3.1 (SYNC), U7.4 (OUT1)
SYNC_PHASE2: TP41.1, U7.5 (OUT2), U13.1 (SYNC)
SYNC_PHASE3: TP27.1, U1.1 (SYNC), U7.6 (OUT3)
WDT_WDI_Jetson: C73.1, J6.14, J6.16, R146.2, TP46.1, TP54.1
WDT_WDI_OBC: C79.1, J10.16, R162.2, TP59.1
~WD_EN_JETSON: JP3.2 (B), R1.2
~WD_EN_OBC: JP4.2 (B), R3.2
